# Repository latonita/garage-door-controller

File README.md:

# garage-door-controller
Garage door controller with integrated motor driver 24V/36V, 7A

Features:
- DRV8701 driver
   - selectable mosfet gate drive
   - and overcurrent protection
- PowerSO mosfets
  - shall be enough to run 24V/7A and more
- External interface for common RF-receivers
  - RX-480R / RF11A04 
  - HCS301 based
- Fabrication
  - Prepared for automated assembly on JLCPCB
  - Most of components are basic, no unnesessary Pick-and-place feeding fees. I personally order only couple of Extended parts to be soldered.

# under construction

# BOM

[Interactive BOM](https://raw.githack.com/latonita/garage-door-controller/refs/heads/main/kicad-project/bom/ibom.html)

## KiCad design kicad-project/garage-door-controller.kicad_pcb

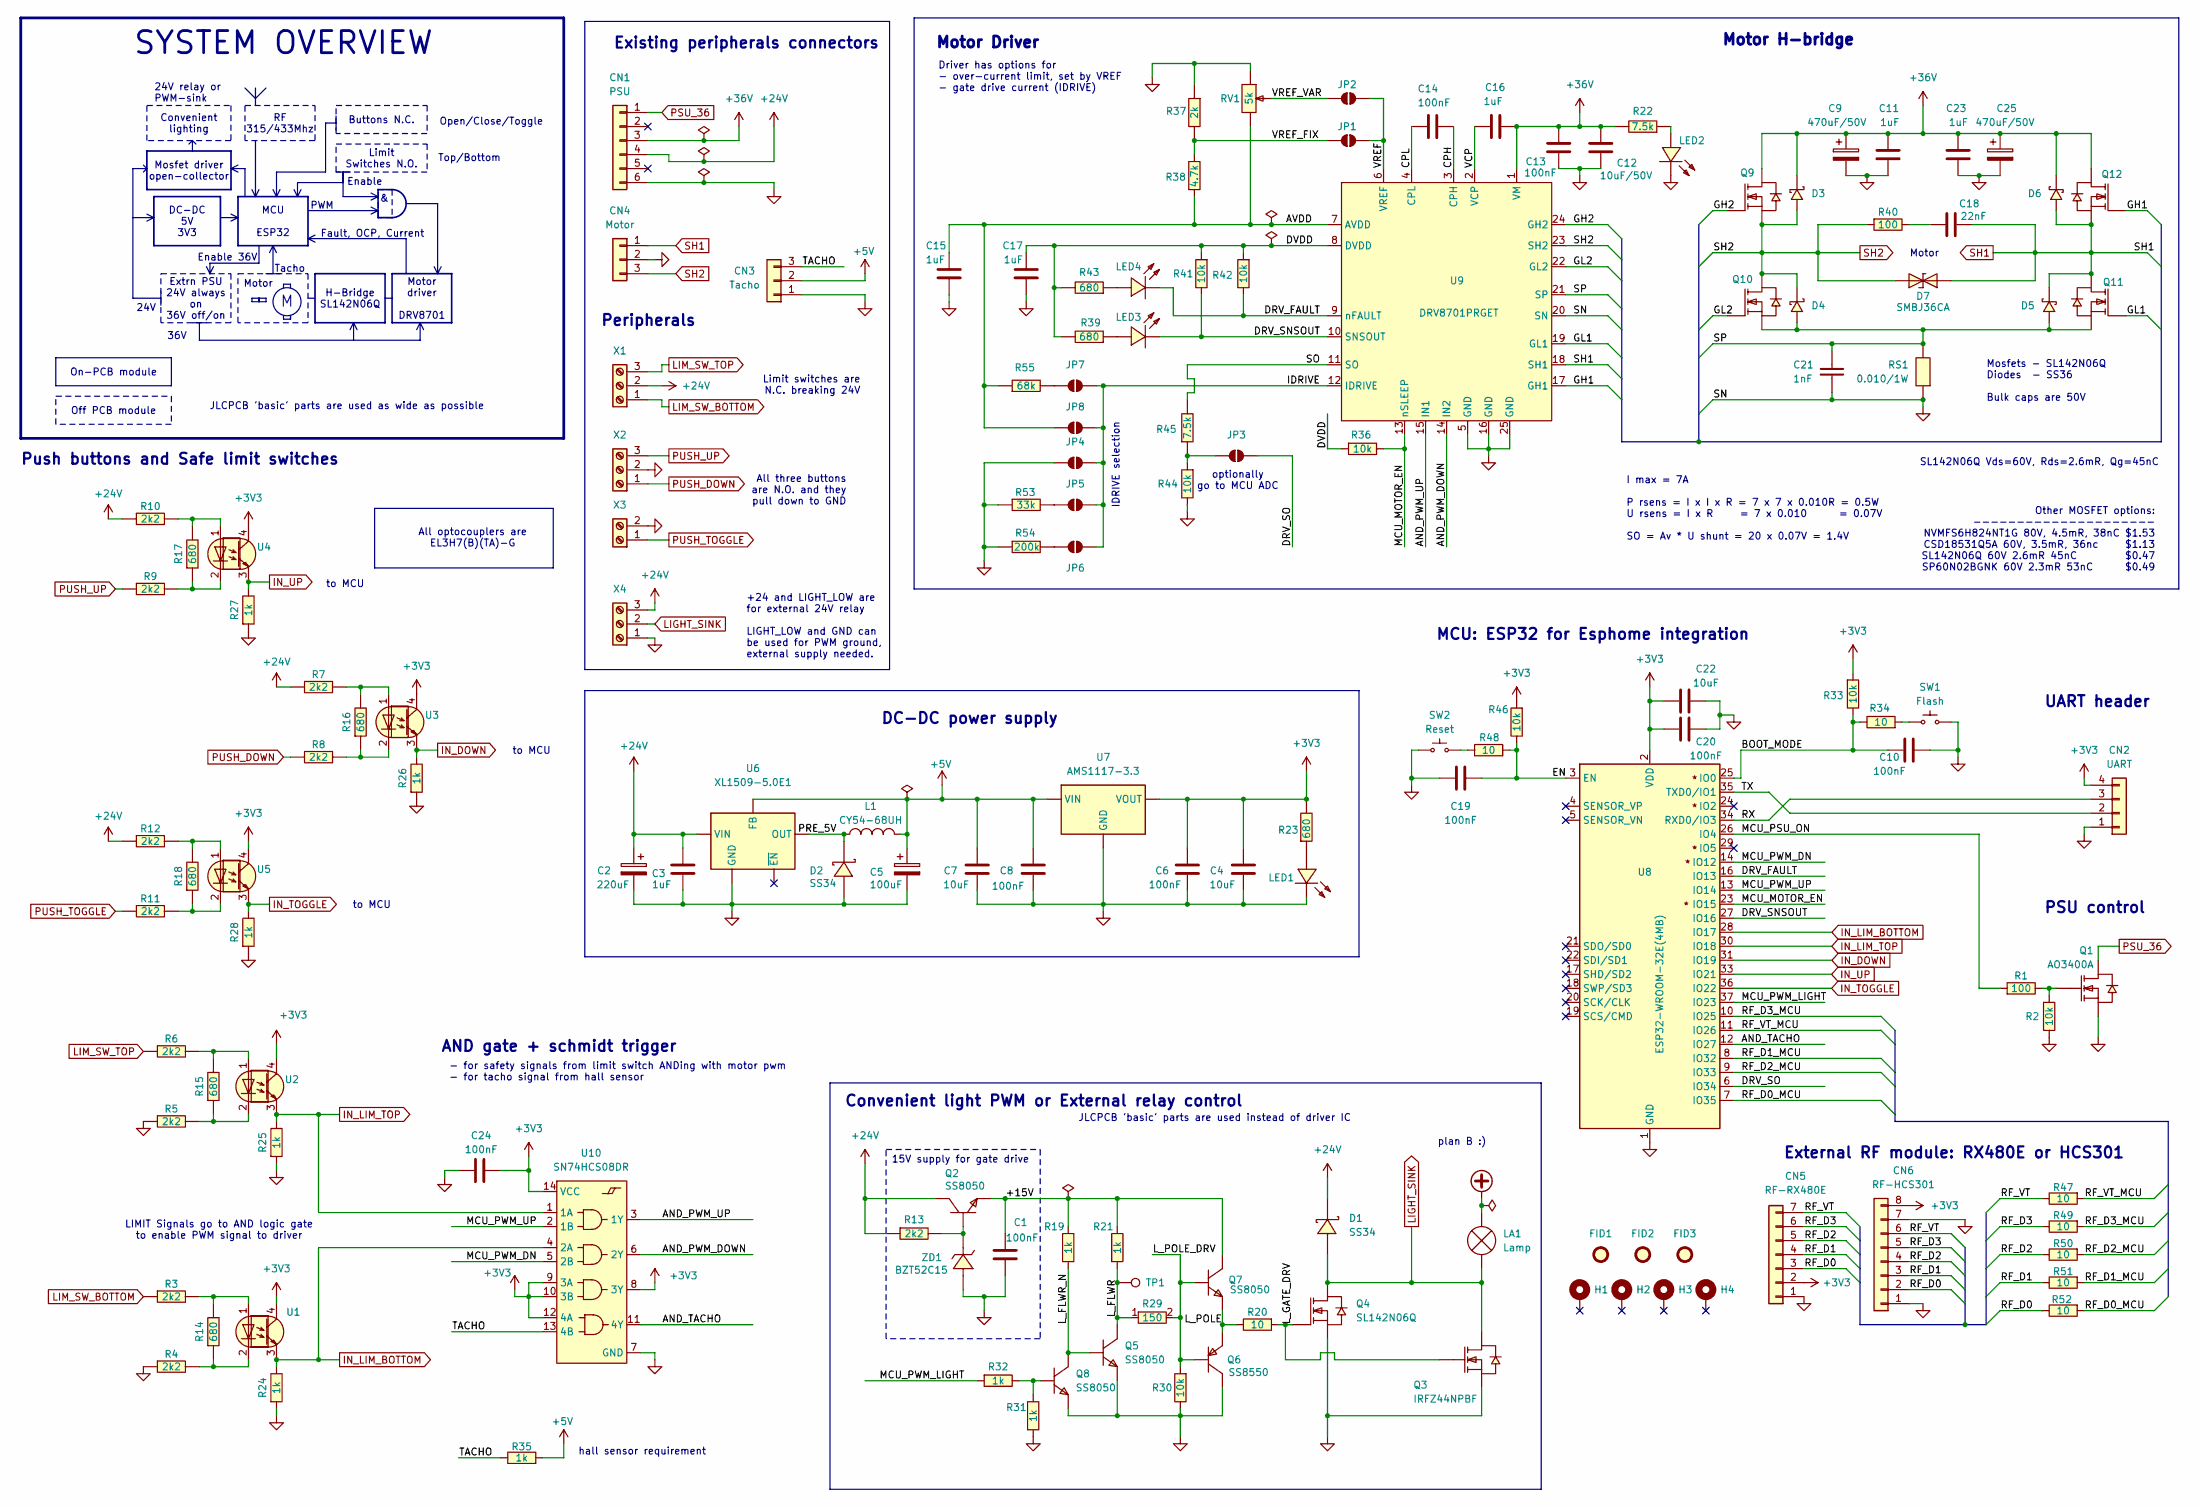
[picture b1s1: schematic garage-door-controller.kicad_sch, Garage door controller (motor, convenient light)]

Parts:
C1, C6, C8, C10, C13, C14, C19, C20, C24: 100nF; C0603; LCSC Part C14663
C2: 220uF; CAP-TH_BD8.0-P3.50-D0.6-FD; LCSC Part C106697
C3, C11, C15, C16, C17, C23: 1uF; C0603; LCSC Part C15849
C4, C7, C22: 10uF; C0603; LCSC Part C19702
C5: 100uF; CASE-B_3528; LCSC Part C16133
C9, C25: 470uF/50V; CAP-TH_BD10.0-P5.00-D1.0-FD; LCSC Part C88733
C12: 10uF/50V; C0805; LCSC Part C440198
C18: 22nF; C0603; LCSC Part C21122
C21: 1nF; C0603; LCSC Part C1588
CN1: PSU; CONN-TH_6P-P5.08_CH5.08-6A; LCSC Part C76512
CN2: UART; PinHeader_1x04_P2.54mm_Vertical
CN3: Tacho; PinHeader_1x03_P2.54mm_Vertical
CN4: Motor; CONN-TH_CH5.08-3A; LCSC Part C23514
CN5: RF-RX480E; PinSocket_1x07_P2.54mm_Vertical; LCSC Part C22438157
CN6: RF-HCS301; PinSocket_1x08_P2.54mm_Vertical; LCSC Part C27438
D1, D2: SS34; SMA_L4.3-W2.6-LS5.2-RD; LCSC Part C8678
D3, D4, D5, D6: SS36; SMA_L4.3-W2.6-LS5.2-RD; LCSC Part C16015
D7: SMBJ36CA; SMB_L4.6-W3.6-LS5.3-BI; LCSC Part C78421
FID1, FID2, FID3: Fiducial; Fiducial_1mm_Mask2mm
H1, H2, H3, H4: MountingHole; MountingHole_3.2mm_M3_DIN965_Pad
JP1, JP2, JP3, JP4, JP5, JP6, JP7, JP8: SolderJumper_2_Open; SolderJumper-2_P1.3mm_Open_RoundedPad1.0x1.5mm
L1: CY54-68UH; IND-SMD_L5.8-W5.2; LCSC Part C2929435
LA1: Lamp
LED1, LED2, LED3, LED4: KT-0603R; LED0603-RD; LCSC Part C2286
Q1: AO3400A; SOT-23-3_L2.9-W1.3-P1.90-LS2.4-BR; LCSC Part C20917
Q2, Q5, Q7, Q8: SS8050; SOT-23-3_L2.9-W1.3-P1.90-LS2.4-BR; LCSC Part C2150
Q3: IRFZ44NPBF; TO-220-3_L10.0-W4.5-P2.54-L; LCSC Part C2586
Q4, Q9, Q10, Q11, Q12: SL142N06Q; PDFN-8_L5.9-W5.2-P1.27-LS6.2-BL; LCSC Part C18208610
Q6: SS8550; SOT-23-3_L2.9-W1.3-P1.90-LS2.4-BR; LCSC Part C8542
R1, R40: 100; R0603; LCSC Part C22775
R2, R30, R33, R36, R41, R42, R44, R46: 10k; R0603; LCSC Part C25804
R3, R4, R5, R6, R7, R8, R9, R10, R11, R12, R13: 2k2; R0603; LCSC Part C4190
R14, R15, R16, R17, R18, R23, R39, R43: 680; R0603; LCSC Part C23228
R19, R21, R24, R25, R26, R27, R28, R31, R32, R35: 1k; R0603; LCSC Part C21190
R20, R34, R47, R48, R49, R50, R51, R52: 10; R0603; LCSC Part C22859
R22, R45: 7.5k; R0603; LCSC Part C23234
R29: 150; R0603; LCSC Part C22808
R37: 2k; R0603; LCSC Part C22975
R38: 4.7k; R0603; LCSC Part C23162
R53: 33k; R0603; LCSC Part C4216
R54: 200k; R0603; LCSC Part C25811
R55: 68k; R0603; LCSC Part C23231
RS1: 0.010/1W; R2512; LCSC Part C393072
RV1: 5k; RES-ADJ-TH_3296W; LCSC Part C60620
SW1, SW2: TS-1187A-B-A-B; SW-SMD_4P-L5.1-W5.1-P3.70-LS6.5-TL_H1.5; LCSC Part C318884
TP1: TestPoint; TestPoint_Pad_D1.5mm
U1, U2, U3, U4, U5: EL3H7(B)(TA)-G; SOP-4_L4.4-W2.8-P1.27-LS7.0-TL; LCSC Part C32565
U6: XL1509-5.0E1; SOIC-8_L5.0-W4.0-P1.27-LS6.0-BL; LCSC Part C61063
U7: AMS1117-3.3; SOT-223-3_L6.5-W3.4-P2.30-LS7.0-BR; LCSC Part C6186
U8: ESP32-WROOM-32E(4MB); WIFI-SMD_ESP32-WROOM-32E; LCSC Part C701341
U9: DRV8701PRGET; VQFN-24_L4.0-W4.0-P0.50-TL-EP2.8; LCSC Part C2150478
U10: SN74HCS08DR; SOIC-14_L8.7-W3.9-P1.27-LS6.0-BL; LCSC Part C2868021
X1, X2, X4: WJ500V-5.08-3P-14-00A; CONN-TH_3P-P5.00_WJ500V-5.08-3P; LCSC Part C72334
X3: WJ500V-5.08-2P-14-00A; CONN-TH_2P-P5.00_WJ500V-5.08-2P; LCSC Part C8465
ZD1: BZT52C15; SOD-123_L2.7-W1.6-LS3.8-RD; LCSC Part C2932746

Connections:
+3V3: C4.2, C6.2, C20.1, C22.1, C24.1, CN2.4, CN5.2, CN6.8, R23.2, R33.1, R46.1, U1.4, U2.4, U3.4, U4.4, U5.4, U7.2 (VOUT), U7.4 (TAB), U8.2 (VDD), U10.8 (3Y), U10.9 (3A), U10.10 (3B), U10.12 (4A), U10.14 (VCC)
+5V: C5.1, C7.2, C8.2, CN3.2, L1.2, R35.1, U6.3 (FB), U7.3 (VIN)
+24V: C2.1, C3.2, CN1.4, D1.1 (K), Q2.3 (C), R7.1, R10.1, R12.1, R13.1, U6.1 (VIN), X1.2, X4.3
+36V: C9.1, C11.2, C12.2, C13.1, C16.2, C23.2, C25.1, CN1.3, D3.1 (K), D6.1 (K), Q9.5 (D), Q9.6 (D), Q9.7 (D), Q9.8 (D), Q9.9 (D), Q12.5 (D), Q12.6 (D), Q12.7 (D), Q12.8 (D), Q12.9 (D), R22.2, U9.1 (VM)
/+15V: C1.2, Q2.2 (E), Q7.3 (C), R19.2, R21.2
/AND_PWM_DOWN: U9.14 (IN2), U10.6 (2Y)
/AND_PWM_UP: U9.15 (IN1), U10.3 (1Y)
/AND_TACHO: U8.12 (IO27), U10.11 (4Y)
/AVDD: C15.2, JP8.1 (A), R38.1, R55.1, RV1.1, U9.7 (AVDD)
/BOOT_MODE: C10.1, R33.2, R34.2, U8.25 (IO0)
/CPH: C14.1, U9.3 (CPH)
/CPL: C14.2, U9.4 (CPL)
/DRV_FAULT: LED4.1 (K), R42.2, U8.16 (IO13), U9.9 (nFAULT)
/DRV_SNSOUT: LED3.1 (K), R41.2, U8.27 (IO16), U9.10 (SNSOUT)
/DRV_SO: JP3.1 (A), U8.6 (IO34)
/DVDD: C17.2, R36.1, R39.2, R41.1, R42.1, R43.2, U9.8 (DVDD)
/EN: C19.1, R46.2, R48.1, U8.3 (EN)
/GH1: Q12.4 (G), U9.17 (GH1)
/GH2: Q9.4 (G), U9.24 (GH2)
/GL1: Q11.4 (G), U9.19 (GL1)
/GL2: Q10.4 (G), U9.22 (GL2)
/IDRIVE: JP4.2 (B), JP5.2 (B), JP6.2 (B), JP7.2 (B), JP8.2 (B), U9.12 (IDRIVE)
/L_FLWR: Q5.3 (C), R21.1, R29.1, TP1.1
/L_FLWR_N: Q5.1 (B), Q8.3 (C), R19.1
/L_GATE_DRV: Q3.1 (G), Q4.4 (G), R20.1
/L_POLE: Q6.2 (E), Q7.2 (E), R20.2
/L_POLE_DRV: Q6.1 (B), Q7.1 (B), R29.2, R30.1
/MCU_MOTOR_EN: R36.2, U8.23 (IO15), U9.13 (nSLEEP)
/MCU_PSU_ON: R1.1, U8.26 (IO4)
/MCU_PWM_DN: U8.14 (IO12), U10.5 (2B)
/MCU_PWM_LIGHT: R32.1, U8.37 (IO23)
/MCU_PWM_UP: U8.13 (IO14), U10.2 (1B)
/PRE_5V: D2.1 (K), L1.1, U6.2 (OUT)
/RF_D0: CN5.3, CN6.2, R52.2
/RF_D0_MCU: R52.1, U8.7 (IO35)
/RF_D1: CN5.4, CN6.3, R51.2
/RF_D1_MCU: R51.1, U8.8 (IO32)
/RF_D2: CN5.5, CN6.4, R50.2
/RF_D2_MCU: R50.1, U8.9 (IO33)
/RF_D3: CN5.6, CN6.5, R49.2
/RF_D3_MCU: R49.1, U8.10 (IO25)
/RF_VT: CN5.7, CN6.6, R47.2
/RF_VT_MCU: R47.1, U8.11 (IO26)
/RX: CN2.3, U8.34 (RXD0/IO3)
/SO: R45.2, U9.11 (SO)
/SP: C21.2, D4.2 (A), D5.2 (A), Q10.1 (S), Q10.2 (S), Q10.3 (S), Q11.1 (S), Q11.2 (S), Q11.3 (S), RS1.2, U9.21 (SP)
/TACHO: CN3.3, R35.2, U10.13 (4B)
/TX: CN2.2, U8.35 (TXD0/IO1)
/VCP: C16.1, U9.2 (VCP)
/VREF: JP1.2 (B), JP2.2 (B), U9.6 (VREF)
/VREF_FIX: JP1.1 (A), R37.2, R38.2
/VREF_VAR: JP2.1 (A), RV1.2
GND: C1.1, C2.2, C3.1, C4.1, C5.2, C6.1, C7.1, C8.1, C9.2, C10.2, C11.1, C12.1, C13.2, C15.1, C17.1, C19.2, C20.2, C21.1, C22.2, C23.1, C24.2, C25.2, CN1.6, CN2.1, CN3.1, CN4.2, CN5.1, CN6.1, CN6.7, D2.2 (A), JP4.1 (A), LED1.1 (K), LED2.1 (K), Q1.2 (S), Q3.3 (S), Q4.1 (S), Q4.2 (S), Q4.3 (S), Q5.2 (E), Q6.3 (C), Q8.2 (E), R2.2, R4.1, R5.1, R24.1, R25.1, R26.1, R27.1, R28.1, R30.2, R31.1, R37.1, R44.2, R53.1, R54.1, RS1.1, RV1.3, SW1.1 (A), SW1.2 (B), SW2.1 (A), SW2.2 (B), U6.5 (GND), U6.6 (GND), U6.7 (GND), U6.8 (GND), U7.1 (GND), U8.1 (GND), U8.15 (GND), U8.38 (GND), U8.39 (GND), U9.5 (GND), U9.16 (GND), U9.20 (SN), U9.25 (GND), U10.7 (GND), X2.2, X3.2, X4.1, ZD1.2 (A)
IN_DOWN: R26.2, U3.3, U8.31 (IO19)
IN_LIM_BOTTOM: R24.2, U1.3, U8.28 (IO17), U10.4 (2A)
IN_LIM_TOP: R25.2, U2.3, U8.30 (IO18), U10.1 (1A)
IN_TOGGLE: R28.2, U5.3, U8.36 (IO22)
IN_UP: R27.2, U4.3, U8.33 (IO21)
LIM_SW_BOTTOM: R3.1, X1.1
LIM_SW_TOP: R6.1, X1.3
unnamed: C18.1, R40.2
unnamed: JP3.2 (B), R44.1, R45.1
unnamed: JP5.1 (A), R53.2
unnamed: JP6.1 (A), R54.2
unnamed: JP7.1 (A), R55.2
unnamed: LED1.2 (A), R23.1
unnamed: LED2.2 (A), R22.1
unnamed: LED3.2 (A), R39.1
unnamed: LED4.2 (A), R43.1
unnamed: Q1.1 (G), R1.2, R2.1
unnamed: Q2.1 (B), R13.2, ZD1.1 (K)
unnamed: Q8.1 (B), R31.2, R32.2
unnamed: R10.2, R17.2, U4.1
unnamed: R11.2, R18.1, U5.2
unnamed: R12.2, R18.2, U5.1
unnamed: R4.2, R14.1, U1.2
unnamed: R3.2, R14.2, U1.1
unnamed: R5.2, R15.1, U2.2
unnamed: R6.2, R15.2, U2.1
unnamed: R8.2, R16.1, U3.2
unnamed: R7.2, R16.2, U3.1
unnamed: R9.2, R17.1, U4.2
unnamed: R34.1, SW1.3 (C), SW1.4 (D)
unnamed: R48.2, SW2.3 (C), SW2.4 (D)
PSU_36: CN1.1, Q1.3 (D)
PUSH_DOWN: R8.1, X2.1
PUSH_TOGGLE: R11.1, X3.1
PUSH_UP: R9.1, X2.3
SH1: C18.2, CN4.1, D5.1 (K), D6.2 (A), D7.1 (K), Q11.5 (D), Q11.6 (D), Q11.7 (D), Q11.8 (D), Q11.9 (D), Q12.1 (S), Q12.2 (S), Q12.3 (S), U9.18 (SH1)
SH2: CN4.3, D3.2 (A), D4.1 (K), D7.2 (A), Q9.1 (S), Q9.2 (S), Q9.3 (S), Q10.5 (D), Q10.6 (D), Q10.7 (D), Q10.8 (D), Q10.9 (D), R40.1, U9.23 (SH2)

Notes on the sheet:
JLCPCB 'basic' parts are used as wide as possible
All optocouplers are EL3H7(B)(TA)-G
Motor H-bridge
Top/Bottom
Enable
Other MOSFET options: --------------------- NVMFS6H824NT1G 80V, 4.5mR, 38nC $1.53 CSD18531Q5A 60V, 3.5mR, 36nc $1.13 SL142N06Q 60V 2.6mR 45nC $0.47 SP60N02BGNK 60V 2.3mR 53nC $0.49
IDRIVE selection
DC-DC power supply
Peripherals
Tacho
36V
PSU control
hall sensor requirement
to MCU
JLCPCB 'basic' parts are used instead of driver IC
Motor
Enable 36V
SYSTEM OVERVIEW
Existing peripherals connectors
All three buttons are N.O. and they pull down to GND
MCU: ESP32 for Esphome integration
plan B :)
optionally go to MCU ADC
Driver has options for - over-current limit, set by VREF - gate drive current (IDRIVE)
PWM
Fault, OCP, Current
Mosfets - SL142N06Q Diodes - SS36 Bulk caps are 50V
Convenient light PWM or External relay control
+24 and LIGHT_LOW are for external 24V relay LIGHT_LOW and GND can be used for PWM ground, external supply needed.
UART header
Limit switches are N.C. breaking 24V
Open/Close/Toggle
SL142N06Q Vds=60V, Rds=2.6mR, Qg=45nC
AND gate + schmidt trigger
External RF module: RX480E or HCS301
24V relay or PWM-sink
- for safety signals from limit switch ANDing with motor pwm - for tacho signal from hall sensor
24V
I max = 7A P rsens = I x I x R = 7 x 7 x 0.010R = 0.5W U rsens = I x R = 7 x 0.010 = 0.07V SO = Av * U shunt = 20 x 0.07V = 1.4V
LIMIT Signals go to AND logic gate to enable PWM signal to driver

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
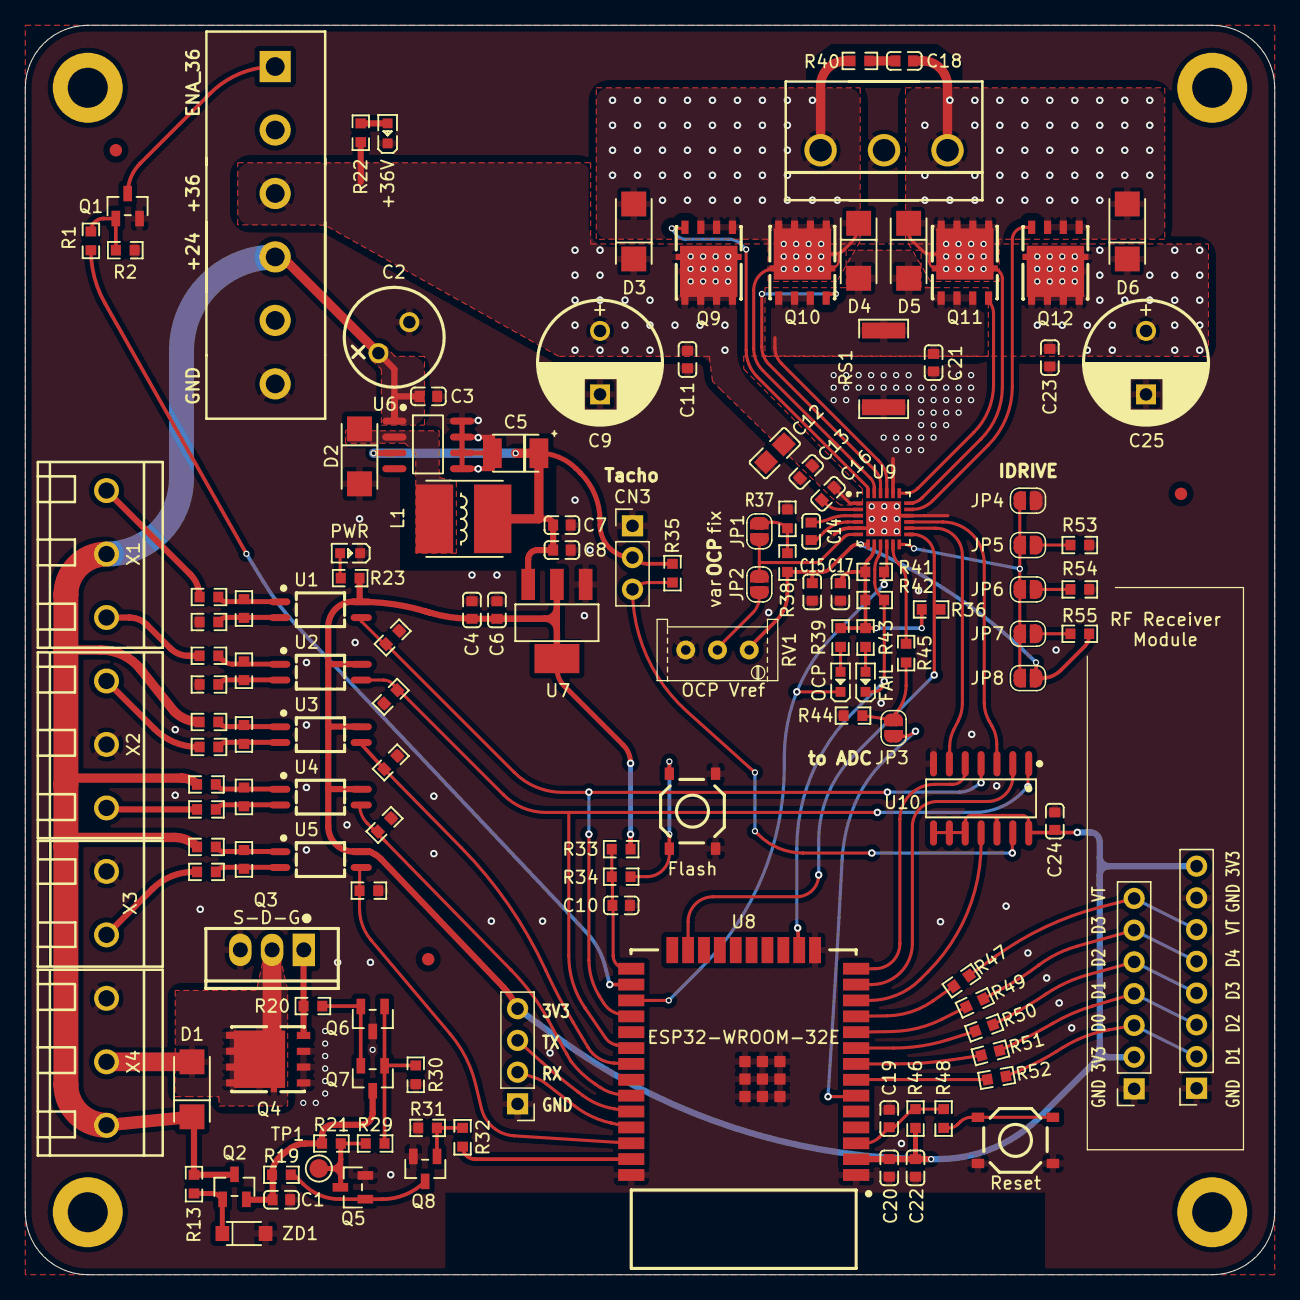
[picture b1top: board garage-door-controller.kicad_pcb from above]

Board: 2 copper layers, 100.0 x 100.0 mm, 145 parts (1 on the bottom side), 91 nets.

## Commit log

2025-03-04 alfa ver
2025-03-05 readme upd
2025-03-14 minor
